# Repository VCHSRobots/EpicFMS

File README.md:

### The EPIC FMS 
**Sept 2021 EPIC Robotz**

This repository stores code that implements a field management system (FMS) for a simple game hosted by EPIC Robots. 

The game consists of robots shooting at various targets during a match. All targets have electronic sensors to detect hits.  The hits are counted at each target and then reported back to a central server, called the "EpicFMS server".  The EpicFMS server talleys the score and provides that information via MQTT and on a website that the EpicFMS hosts.  

The website that is hosted by EpciFMS server actually has two interfaces: the scoreboard and the game management interface.  The game management interface allows game administors to start, stop, reset the game.  Game parameters can also be set through the game management interface.

Finally, the EpicFMS server sends game status and commands back to the field elements -- mainly to control LEDs while the game is being played.

This repository contains all code and documentation for this system, including the code for the EpicFMS website, and the code for the electronics in the various targets. 

### Block Diagram

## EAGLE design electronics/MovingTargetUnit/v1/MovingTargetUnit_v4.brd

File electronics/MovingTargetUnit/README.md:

### PCB for Moving Tareget Unit
**Oct 2021 EPIC Robotz**

As of 10/6/21, Two PCBs have been manufactured:

Verion 1:  Submitted for manufacturing on Friday, 9/24/21. Recived on 10/1/21.  This was based on V4 of the schematic.
Problems found:
1. Voltagle regulars overheat.  Since one of these powers sensors as well as neopixles, entire circult fails in about 2 minutes.
2. The outputs of the IR detectors are wired to pins that must be held in special conditions during startup -- this causes boot up problems.
3. The USB power flows back into the voltage regulators, causing confusion during developement.  Also, since USB power is tied directly
to input battery terminals, damage to a host computer might be possible during development.
4. The NEO pixels are driven directly from the ESP9266, at 3.3v.  It should be closer to 5v for reliable operation.

Verion 2: Submitted for manufacturing on Tuesday, 10/5/21.  This was based on V5 of the schematic. 
Hopefully, above problems fixed.

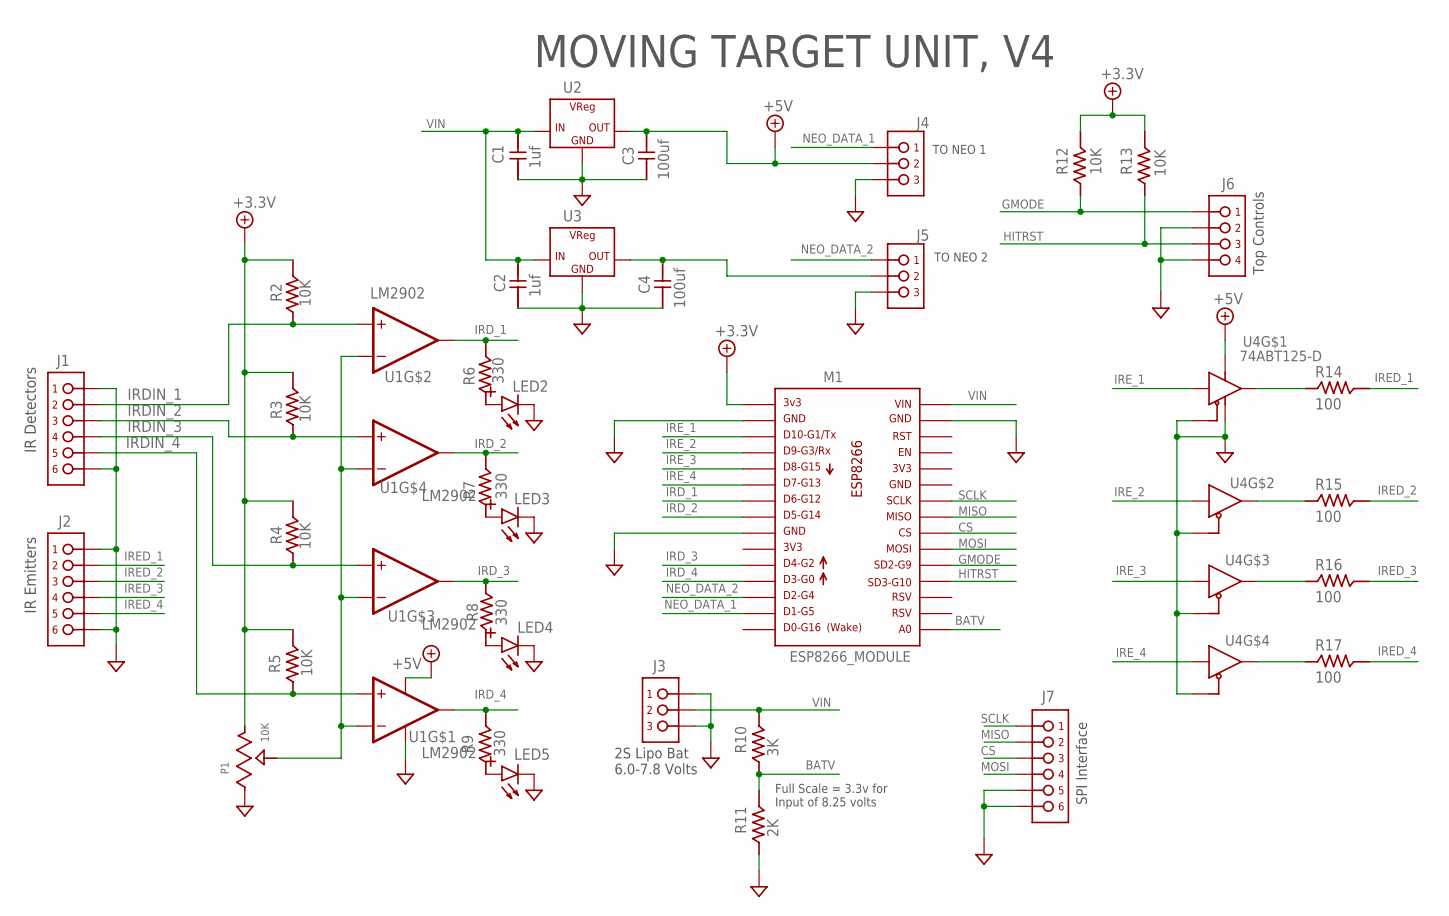
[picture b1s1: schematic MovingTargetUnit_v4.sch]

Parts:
C1, C2: 1uf; C1206
C3, C4: 100uf; C1206
J1, J2, J7: PINHDR_1X6-JST; JST-XH_098_VERT_1X6
J3, J4, J5: PINHDR_1X3XH-JST; JST-XH_098_VERT_1X3
J6: PINHDR_1X4-JST; JST-XH_098_VERT_1X4
LED2, LED3, LED4, LED5: LED1206; LED_1206
M1: ESP8266_MODULE
P1: 10K; TRIMPOT_3361P
R2, R3, R4, R5, R12, R13: 10K; R1206
R6, R7, R8, R9: 330; R1206
R10: 3K; R1206
R11: 2K; R1206
R14, R15, R16, R17: 100; R1206
U1: LM2902; SO16LNB-14PIN
U2, U3: VREG-3L7805CDT; TO252-3
U4: 74ABT125-D; SO16LNB-14PIN

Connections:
+3.3V: M1.P$1, P1.3, R2.P$2 (2), R3.P$2 (2), R4.P$2 (2), R5.P$2 (2), R12.P$2 (2), R13.P$2 (2)
+5V: C3.P$2 (2), J4.2, U1.P$4 (P+), U2.3 (OUT), U4.P$14 (VCC)
BATV: M1.P$16, R10.P$1 (1), R11.P$2 (2)
CS: J7.4 (3), M1.P$22
GMODE: J6.1, M1.P$20, R12.P$1 (1)
GND: C1.P$1 (1), C2.P$1 (1), C3.P$1 (1), C4.P$1 (1), J1.1 (6), J1.6 (1), J2.1 (6), J2.6 (1), J3.1 (3), J3.3 (1), J4.1 (3), J5.1 (3), J6.2, J6.4, J7.1 (6), J7.2 (5), LED2.CATHODE(-) (CATHODE), LED3.CATHODE(-) (CATHODE), LED4.CATHODE(-) (CATHODE), LED5.CATHODE(-) (CATHODE), M1.P$2, M1.P$9, M1.P$29, P1.1, R11.P$1 (1), U1.P$11 (P-), U2.FIN (GND), U3.FIN (GND), U4.P$1 (OE), U4.P$4 (OE), U4.P$7 (GND), U4.P$10 (OE), U4.P$13 (OE)
HITRST: J6.3, M1.P$19, R13.P$1 (1)
IRDIN_1: J1.5 (2), R2.P$1 (1), U1.P$5 (+IN)
IRDIN_2: J1.4 (3), R3.P$1 (1), U1.P$12 (+IN)
IRDIN_3: J1.3 (4), R4.P$1 (1), U1.P$10 (+IN)
IRDIN_4: J1.2 (5), R5.P$1 (1), U1.P$3 (+IN)
IRD_1: M1.P$7, R6.P$2 (2), U1.P$7 (OUT)
IRD_2: M1.P$8, R7.P$2 (2), U1.P$14 (OUT)
IRD_3: M1.P$11, R8.P$1 (1), U1.P$8 (OUT)
IRD_4: M1.P$12, R9.P$2 (2), U1.P$1 (OUT)
IREDD_1: R14.P$1 (1), U4.P$3 (OUT)
IREDD_2: R15.P$1 (1), U4.P$6 (OUT)
IREDD_3: R16.P$1 (1), U4.P$8 (OUT)
IREDD_4: R17.P$1 (1), U4.P$11 (OUT)
IRED_1: J2.5 (2), R14.P$2 (2)
IRED_2: J2.4 (3), R15.P$2 (2)
IRED_3: J2.3 (4), R16.P$2 (2)
IRED_4: J2.2 (5), R17.P$2 (2)
IRE_1: M1.P$3, U4.P$2 (IN)
IRE_2: M1.P$4, U4.P$5 (IN)
IRE_3: M1.P$5, U4.P$9 (IN)
IRE_4: M1.P$6, U4.P$12 (IN)
MISO: J7.5 (2), M1.P$23
MOSI: J7.3 (4), M1.P$21
unnamed: LED3.ANODE(+) (ANODE), R7.P$1 (1)
unnamed: LED2.ANODE(+) (ANODE), R6.P$1 (1)
unnamed: LED4.ANODE(+) (ANODE), R8.P$2 (2)
unnamed: LED5.ANODE(+) (ANODE), R9.P$1 (1)
unnamed: P1.2, U1.P$2 (-IN), U1.P$6 (-IN), U1.P$9 (-IN), U1.P$13 (-IN)
unnamed: C4.P$2 (2), J5.2, U3.3 (OUT)
NEO_DATA_1: J4.3 (1), M1.P$14
NEO_DATA_2: J5.3 (1), M1.P$13
SCLK: J7.6 (1), M1.P$24
VIN: C1.P$2 (2), C2.P$2 (2), J3.2, M1.P$30, R10.P$2 (2), U2.1 (IN), U3.1 (IN)

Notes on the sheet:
TO NEO 1
MOVING TARGET UNIT, V4
TO NEO 2
2S Lipo Bat 6.0-7.8 Volts
Full Scale = 3.3v for Input of 8.25 volts
Top Controls
SPI Interface
IR Detectors
IR Emitters

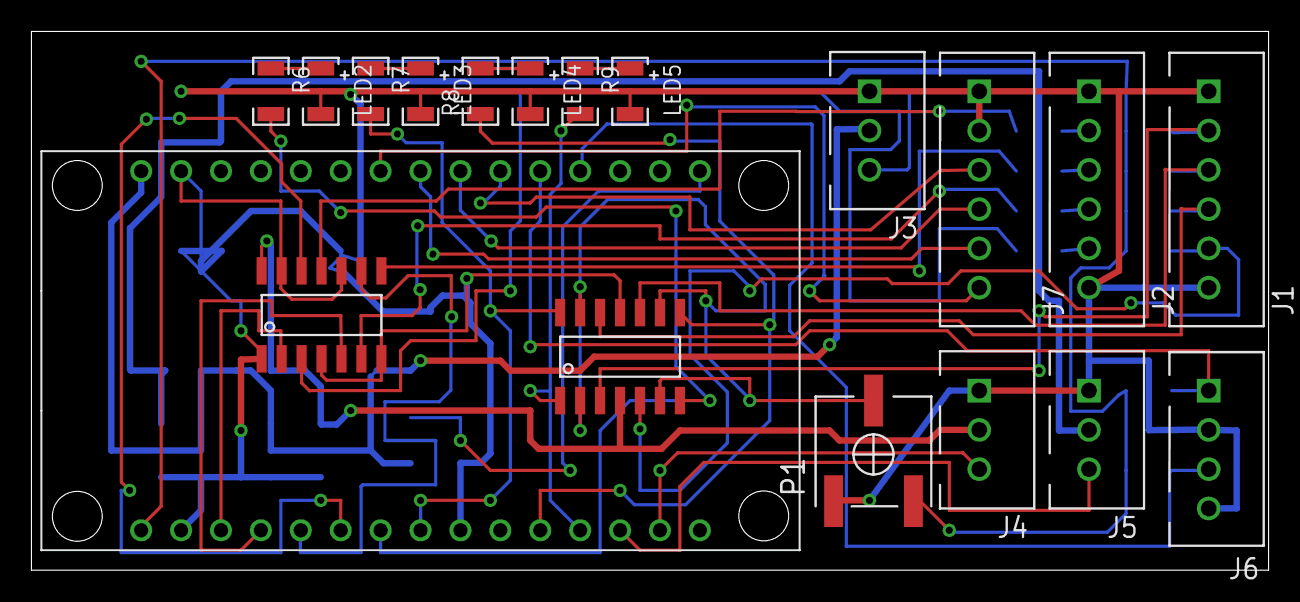
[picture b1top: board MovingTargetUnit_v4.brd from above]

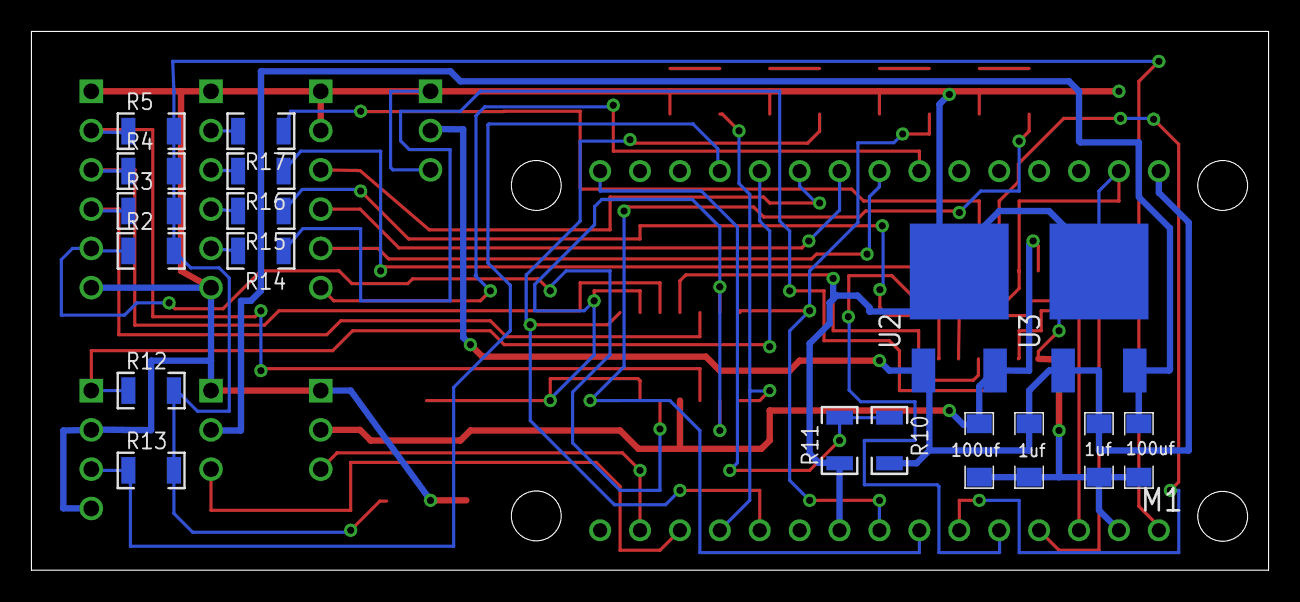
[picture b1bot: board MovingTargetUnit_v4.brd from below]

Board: 2 copper layers, 78.7 x 34.3 mm, 37 parts (18 on the bottom side), 39 nets.

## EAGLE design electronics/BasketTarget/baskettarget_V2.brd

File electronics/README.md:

## Electronics for EpicFMS

This folder contains the data for the electronic components -- including
the custom PCB boards that were manufactured for the hit counters.

Note: Please see the MovingTargeUnit for the PCB -- This PCB is now
targeted to be used in all the targets.

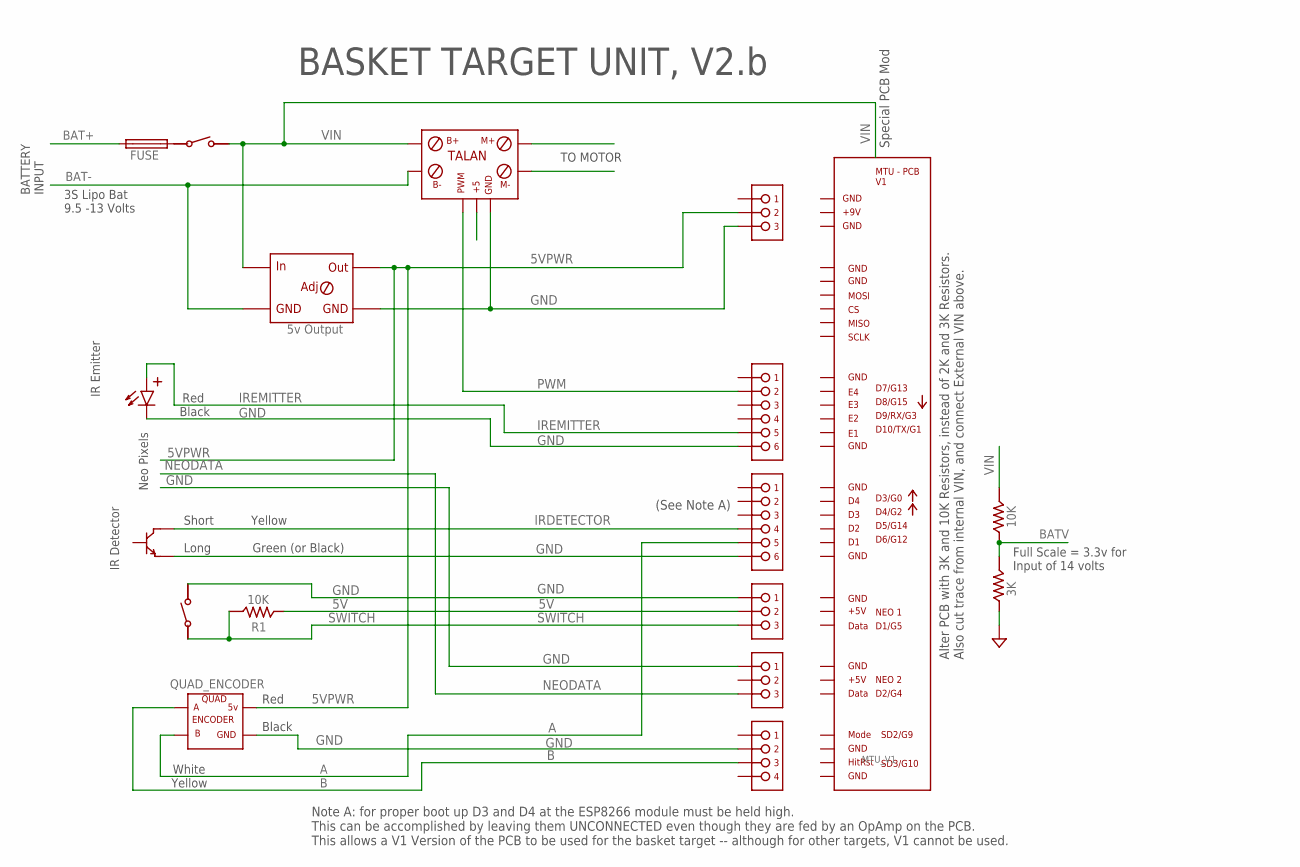
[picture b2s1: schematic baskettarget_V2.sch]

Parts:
F2: FUSE; FUSE_HOLDER_WICKMANN-19596
J1: ENCODER; PINHDR_TH_100_1X4
J2: NEO; PINHDR_TH_100_1X3
J4: INPUTS; PINHDR_TH_100_1X6
J6: OUTPUTS; PINHDR_TH_100_1X6
J7: PWR; PINHDR_TH_100_1X3
J10: SERVO; PINHDR_TH_100_1X3
LED1: IR Emitter; LED-TH100
M1: MTU_V1
M2: TALAN; TALAN_PWM
M4: 5v Output; DC_DC_MODULE
R1, R10: 10K; R300
R11: 3K; R300
S1, S2: TOGGLE_SPST; SPST_TOGGLE
T1: T_NPN; TO-92
U2: QUAD_ENCODER

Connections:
5V: J2.2, R1.P$1 (1)
5VPWR: J7.2, M4.OUT+ (OUT), U2.5V
A: J4.5, U2.B
B: J1.3, U2.A
BAT+: F2.A (1)
BAT-: M2.B-, M4.IN- (G1)
BATV: R10.P$1 (1), R11.P$2 (2)
GND: J1.2, J2.1, J4.6, J6.6, J7.3, J10.1, LED1.P$2 (CATHODE), M2.GND, M4.OUT- (G2), R11.P$1 (1), S1.P$2, T1.P$3 (EMITTER), U2.GND
IRDETECTOR: J4.4, T1.P$1 (COLLECTOR)
IREMITTER: J6.5, LED1.P$1 (ANODE)
unnamed: F2.B (2), S2.P$1
NEODATA: J10.3
PWM: J6.2, M2.PWM
SWITCH: J2.3, R1.P$2 (2), S1.P$1
VIN: M2.B+, M4.IN+ (IN), R10.P$2 (2), S2.P$2

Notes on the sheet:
BASKET TARGET UNIT, V2.b
3S Lipo Bat 9.5 -13 Volts
Full Scale = 3.3v for Input of 14 volts
IR Detector
Long
Short
Yellow
Green (or Black)
BATTERY INPUT
TO MOTOR
Red
Black
Neo Pixels
IR Emitter
Special PCB Mod
Alter PCB with 3K and 10K Resistors, instead of 2K and 3K Resistors. Also cut trace from internal VIN, and connect External VIN above.
Note A: for proper boot up D3 and D4 at the ESP8266 module must be held high. This can be accomplished by leaving them UNCONNECTED even though they are fed by an OpAmp on the PCB. This allows a V1 Version of the PCB to be used for the basket target -- although for other targets, V1 cannot be used.
White
(See Note A)

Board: 2 copper layers, 18 parts (0 on the bottom side), 13 nets, no tracks yet.

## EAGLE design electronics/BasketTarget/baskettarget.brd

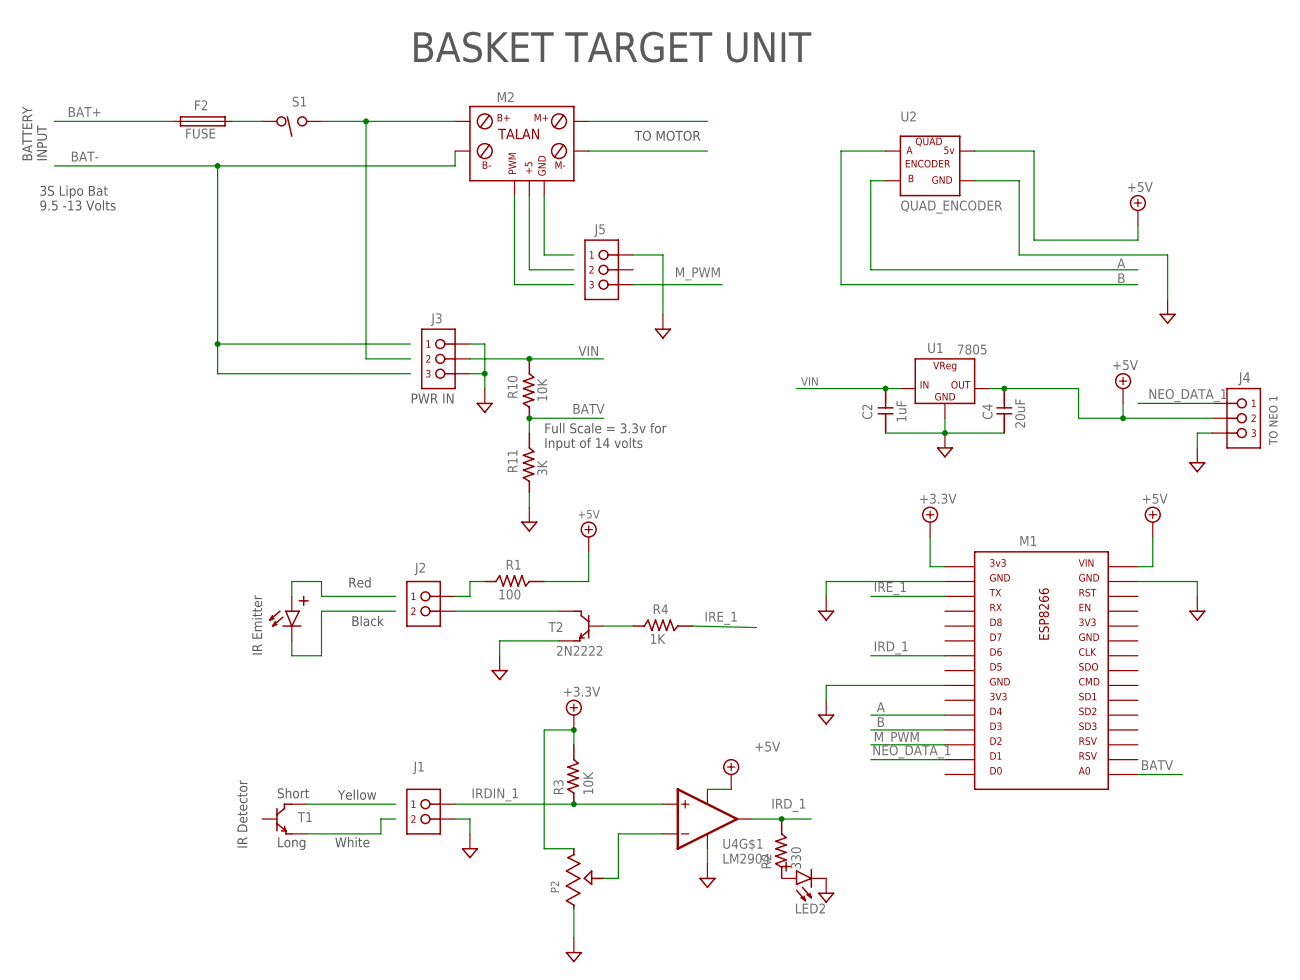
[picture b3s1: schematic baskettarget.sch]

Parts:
C2: 1uF; CAP200
C4: 20uF; CAP200
F2: FUSE; FUSE_HOLDER_WICKMANN-19596
J1, J2: PINHDR_1X2-JST; JST-XH_098_VERT_1X2
J3, J4, J5: PINHDR_1X3XH-JST; JST-XH_098_VERT_1X3
LED1, LED2: LEDTH-DIP-100; LED-TH100
M1: ESP8266_MODULE
M2: TALAN; TALAN_PWM
P2: TRIMPOT-SIP; TRIMPOT_SIP_100
R1: 100; R300
R2: 330; R300
R3, R10: 10K; R300
R4: 1K; R300
R11: 3K; R300
S1: TOGGLE_SWITCH_SPST; SPST_TOGGLE
T1: T_NPN; TO-92
T2: 2N2222; TO-92
U1: 7805; PINHDR_TH_100_1X3
U2: QUAD_ENCODER
U4: LM2904; DIP8

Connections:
+3.3V: M1.P$1, P2.P$3, R3.P$2 (2)
+5V: C4.2, J4.2, M1.P$30, R1.P$2 (2), U1.3 (OUT), U2.5V, U4.P$8 (P+)
A: M1.P$11, U2.B
B: M1.P$12, U2.A
BAT+: F2.A (1)
BAT-: M2.B-
BATV: M1.P$16, R10.P$1 (1), R11.P$2 (2)
GND: C2.1, C4.1, J1.2, J3.1 (3), J3.3 (1), J4.1 (3), J5.3 (1), LED2.P$2 (CATHODE), M1.P$2, M1.P$9, M1.P$29, P2.P$1, R11.P$1 (1), T2.P$3 (EMITTER), U1.2 (GND), U2.GND, U4.P$4 (P-)
IRDIN_1: J1.1, R3.P$1 (1), U4.P$3 (+IN)
IRD_1: M1.P$7, R2.P$2 (2), U4.P$1 (OUT)
IRE_1: M1.P$3, R4.P$2 (2)
M_PWM: J5.1 (3), M1.P$13
unnamed: J2.1, R1.P$1 (1)
unnamed: LED2.P$1 (ANODE), R2.P$1 (1)
unnamed: P2.P$2, U4.P$2 (-IN)
unnamed: F2.B (2), S1.P$1
unnamed: M2.B+, S1.P$3
unnamed: J2.2, T2.P$1 (COLLECTOR)
unnamed: R4.P$1 (1), T2.P$2 (BASE)
NEO_DATA_1: J4.3 (1), M1.P$14
VIN: C2.2, J3.2, R10.P$2 (2), U1.1 (IN)

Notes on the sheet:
TO NEO 1
BASKET TARGET UNIT
3S Lipo Bat 9.5 -13 Volts
Full Scale = 3.3v for Input of 14 volts
IR Detector
IR Emitter
Red
Black
Long
Short
Yellow
White
BATTERY INPUT
TO MOTOR
PWR IN

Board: 2 copper layers, 25 parts (0 on the bottom side), 19 nets, no tracks yet.

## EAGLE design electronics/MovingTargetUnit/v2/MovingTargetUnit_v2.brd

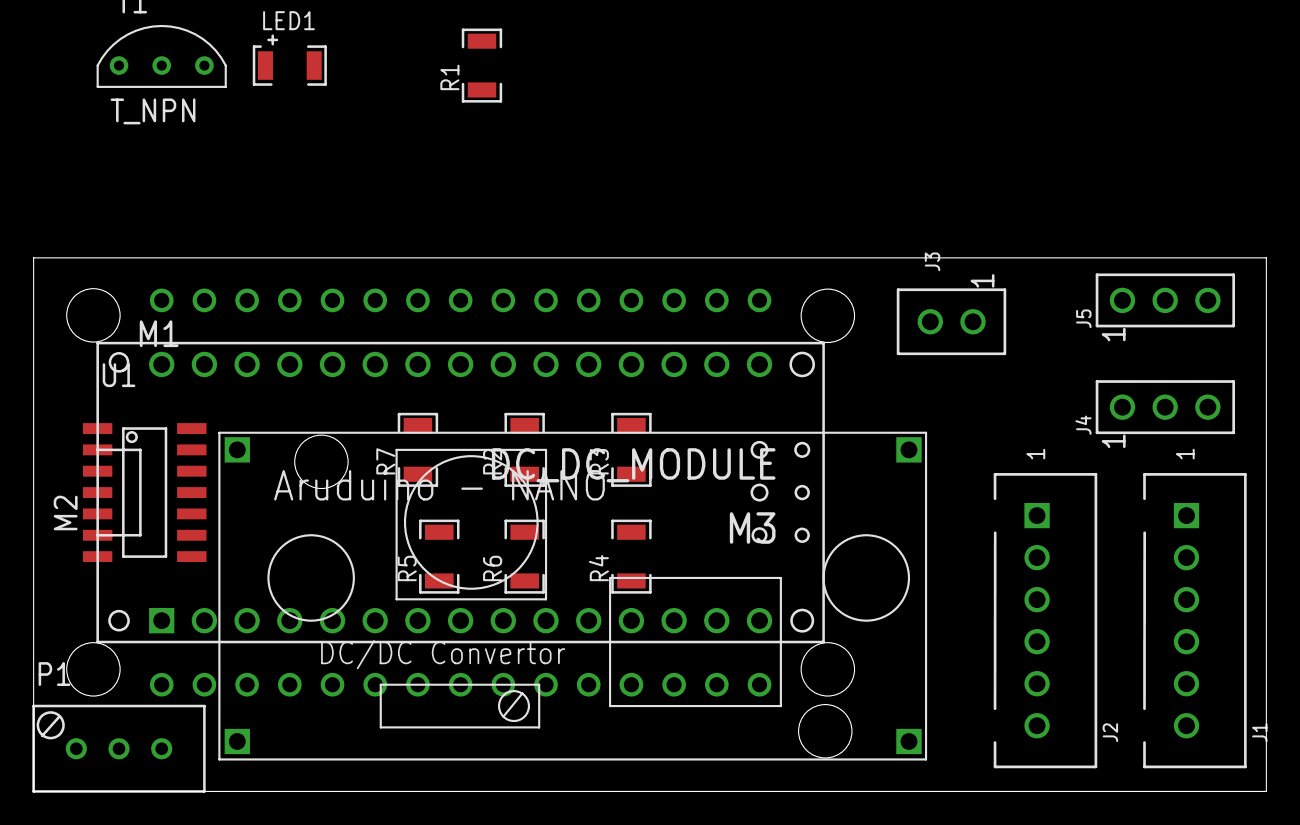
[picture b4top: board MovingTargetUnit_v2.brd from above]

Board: 2 copper layers, 73.3 x 31.7 mm, 19 parts (1 on the bottom side), 26 nets, no tracks yet.

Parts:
J1, J2: PINHDR_1X6-XH; JST-XH_098_VERT_1X6
J3: PINHDR_1X2-100; PINHDR_TH_100_1X2
J4, J5: PINHDR_1X3-100; PINHDR_TH_100_1X3
LED1: IR Emitter LED; LED_1206
M1: ESP8266_MODULE
M2: ARDUINO-NANO
M3: DC_DC_MODULE
P1: 10K; TRIMPOT_SIP_100
R1: 100; R1206
R2: 3K; R1206
R3: 2K; R1206
R4, R5, R6, R7: 10K; R1206
T1: T_NPN; TO-92
U1: SO16LNB-14PIN

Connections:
+5V: M2.5V, P1.P$3, R4.P$2, R5.P$2, R6.P$2, R7.P$2, U1.P$4
BATV: M1.P$16, M2.A0, R2.P$1, R3.P$2
GND: J1.1, J1.2, J2.1, J2.2, J3.2, J4.3, J5.3, LED1.CATHODE(-), M1.P$2, M1.P$9, M1.P$25, M1.P$29, M2.GND, M2.GND2, M3.IN-, M3.OUT-, P1.P$1, R3.P$1, T1.P$3, U1.P$11
IRD_1: M2.D4, U1.P$7
IRD_2: M2.D5, U1.P$14
IRD_3: M2.D6, U1.P$8
IRD_4: M2.D7, U1.P$1
IRE_1: J2.6, M2.D2
IRE_2: J2.5, M2.D3
IRE_3: J2.4, M2.D8
IRE_4: J2.3, M2.D9
unnamed: M2.3.3, M2.REF
unnamed: J1.6, R4.P$1, U1.P$5
unnamed: J1.5, R5.P$1, U1.P$12
unnamed: J1.4, R6.P$1, U1.P$10
unnamed: J1.3, R7.P$1, U1.P$3
unnamed: LED1.ANODE(+), R1.P$1
unnamed: P1.P$2, U1.P$2, U1.P$6, U1.P$9, U1.P$13
NEO_DATA_1: J4.1, M1.P$14
NEO_DATA_2: J5.1, M1.P$15
NEO_PWR: J4.2, J5.2, M3.OUT+
SPI_CLK: M1.P$8, M2.D13
SPI_CS: M1.P$5, M2.D10
SPI_MISO: M1.P$7, M2.D12
SPI_MOSI: M1.P$6, M2.D11
VIN: J3.1, M1.P$30, M2.VIN, M3.IN+, R2.P$2

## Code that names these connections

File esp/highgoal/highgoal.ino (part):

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// #define PIN_NONE    -1  // Means no pin assigned.
// #define PIN_NEO      4  // D2/G4 -- On NEO2 Header -- 
// #define PIN_IRE     15  // 1  // D10/TX/G1 -- IR Emitter
// #define PIN_GMODE    5  // D1/G5 -- On NEO1 Header --
// #define PIN_PWM     13  // D7/G13 -- PWM via 74125 buffer
// #define PIN_IRD     14  // D5/G14 -- IR Detector 
// #define PIN_A       12  // D6/G12 -- Via OpAmp 
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#define PIN_IRE     15  // D8/G15 -- IR Emitter
#define PIN_IRD     12  // D6/G12 -- IR Detector 
#define PIN_A       13  // D7/G13  -- Modified Direct input, via mod 
#define PIN_B       10  // SD3/G10 -- Direct input, Was HitRst button before mod
#define PIN_GMODE   14  // D5/G14  -- Input via OpAmp
#define NPIXELS 43

#define VOLTSPERLSB 0.013 // Volts per bit on analog sensor for V-Battery
#define SW_RUN LOW      // Defines how the switch is used, High=Run 
#define SW_OFFLINE HIGH // Defines how the switch is used, Low=offline  
#define SW_UNDEFINED -1 // Use when the condition of the switch is not known

// Definations for On-board LED.  
#define PIN_ONBOARDLED 16
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  hitdetector.begin();

  Serial.println("Setting up Run Mode switch.");
  pinMode(PIN_GMODE, INPUT);

  Serial.println("Setting up motor.");
  bmotor.begin();
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void loop() {
  mainloop_count++;
  static int lastmode = SW_UNDEFINED;
  mode = digitalRead(PIN_GMODE);
  if (mode != lastmode) { 
   lastmode = mode;
   if (mode == SW_OFFLINE) {
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
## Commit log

2021-09-15 Project Init
2021-09-16 ESP8266 SW Design Coments
2021-09-18 More Docs, First Ring Detector Working
2021-09-18 Minor bug vises
2021-09-21 SPI working
2021-09-22 Added TODO list
2021-09-25 Submit PCB for Moving Target Unit
2021-09-30 Website is born
2021-09-30 continued dev
2021-10-01 work at school
2021-10-02 some work on electronics
2021-10-05 V1 of PCB working
2021-10-06 work at vchs
2021-10-06 Adding CAD files, organizing Work, Documenting
2021-10-07 Basket Target debugging, some success
2021-10-08 work in progress
2021-10-09 FIxing Doc, Fixing Intellasense, New Schematics
2021-10-09 More Fixing up Documentation
2021-10-09 Recovering from big reorg...
2021-10-09 Recompiled PPT
2021-10-10 Don't commit compiler settings
2021-10-11 Motor, Hit Count, Neos working
2021-10-12 problems with quadrature interrupts
2021-10-12 Offline mode for Basket Working
2021-10-13 Lights
2021-10-13 Johnatahan's Code
2021-10-13 New Lights
2021-10-13 from lab
2021-10-13 minor fix with gitignore
2021-10-13 Synced after Lab Work
2021-10-14 Basket almost working fully
2021-10-15 some progress on website
2021-10-16 Power Supply Box Ready for 3D printing
2021-10-16 V1 of python driver for basket target.
2021-10-16 Johnathan emanuelli Oct/16/2021
2021-10-18 Stuff to make Ring Lights for Camera
2021-10-18 Layout of Main Score Board Done
2021-10-18 revamped json between python and javascript
2021-10-18 Additional Grid stuff working on scoreboard
2021-10-18 First Time end-to-end working!
2021-10-19 Some work on admin pages
2021-10-20 10/19/2021
2021-10-20 work at robots
2021-10-20 Power Supply Box, V2
2021-10-21 V3 of PCB working with Test Program
2021-10-22 Doc additions
2021-10-22 More work on slider testing
2021-10-23 Lights Finished 10/23/2021
2021-10-23 Forgot FMSERROR
2021-10-25 IR Beam parts of slider target working
2021-10-25 progress on website
2021-10-26 End-to-End for Sliders..
2021-10-26 queue command working in slider unit
2021-10-26 New logger. Upgrades to ui.
2021-10-27 work in the lab
2021-10-27 New 3D parts for Moving Target
2021-10-29 Moving Target Finshed, both firmware and hardware
2021-10-29 Minor Fixes in firmware
2021-10-29 Backend of FMS working with targets
2021-10-29 some work done on game setup
2021-10-30 Finished game ui. starting on game logic
2021-10-30 EpicFMS Fully Working, ready for shootout
2021-10-30 update game timing
2021-10-30 update to 2:30 mins
2021-11-01 Work on Camera Ring
2021-11-02 Wrapping up before robots on Tues
2021-11-04 Basket hardware/firmware ready for game
2021-11-04 Hardare finialized. Score finished for teleop.
2021-11-10 UI Improvements before game
2021-11-13 its almost done
2021-11-13 fixing bugs
2021-11-14 All known bugs fixed, game ready
2025-11-14 New Version for Epic Side Quest 2025
